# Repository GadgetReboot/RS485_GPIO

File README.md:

# RS485_GPIO
16 Switch Inputs to RS485 Control Outputs
<br><br><BR><BR>

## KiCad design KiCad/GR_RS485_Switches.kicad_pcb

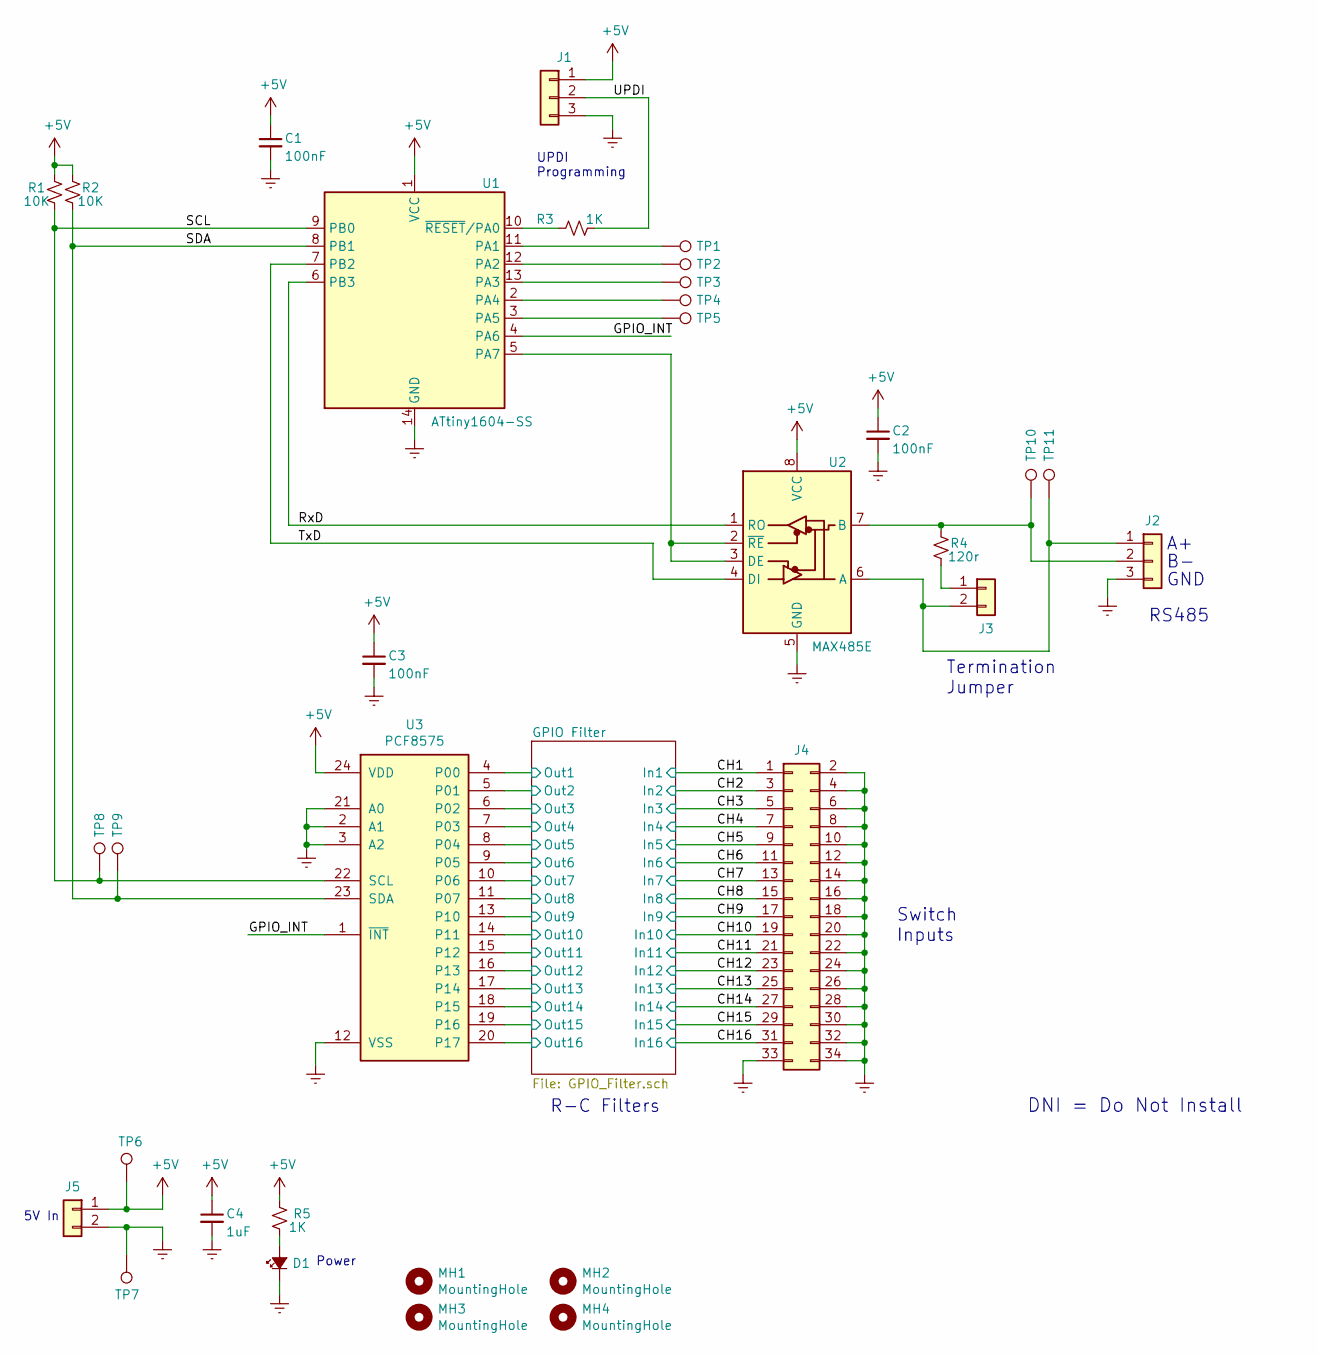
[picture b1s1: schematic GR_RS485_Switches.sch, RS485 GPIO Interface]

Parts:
C1, C2, C3: 100nF; C_0805_2012Metric_Pad1.15x1.40mm_HandSolder
C4: 1uF; C_0805_2012Metric_Pad1.15x1.40mm_HandSolder
D1: LED_Small_ALT; LED_0805_2012Metric_Pad1.15x1.40mm_HandSolder
J1: Conn_01x03; PinHeader_1x03_P2.54mm_Vertical
J2: Conn_01x03; JST_XH_S3B-XH-A-1_1x03_P2.50mm_Horizontal
J3: Conn_01x02; PinHeader_1x02_P2.54mm_Vertical
J4: Conn_02x17_Odd_Even; IDC-Header_2x17_P2.54mm_Vertical
J5: Conn_01x02; JST_XH_S2B-XH-A-1_1x02_P2.50mm_Horizontal
MH1, MH2, MH3, MH4: MountingHole; MountingHole_3.7mm
R1, R2: 10K; R_0805_2012Metric_Pad1.15x1.40mm_HandSolder
R3, R5: 1K; R_0805_2012Metric_Pad1.15x1.40mm_HandSolder
R4: 120r; R_0805_2012Metric_Pad1.15x1.40mm_HandSolder
TP1, TP2, TP3, TP4, TP5, TP6, TP7, TP8, TP9, TP10, TP11: TestPoint; TestPoint_Pad_D1.0mm
U1: ATtiny1604-SS; SOIC-14_3.9x8.7mm_P1.27mm
U2: MAX485E; SOIC-8_3.9x4.9mm_P1.27mm
U3: PCF8575; SOIC-24W_7.5x15.4mm_P1.27mm

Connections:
+5V: C1.1, C2.1, C3.1, C4.1, J1.1, J5.1, R1.2, R2.2, R5.2, TP6.1, U1.1 (VCC), U2.8 (VCC), U3.24 (VDD)
/CH1: J4.1; also elsewhere on the board
/CH2: J4.3; also elsewhere on the board
/CH3: J4.5; also elsewhere on the board
/CH4: J4.7; also elsewhere on the board
/CH5: J4.9; also elsewhere on the board
/CH6: J4.11; also elsewhere on the board
/CH7: J4.13; also elsewhere on the board
/CH8: J4.15; also elsewhere on the board
/CH9: J4.17; also elsewhere on the board
/CH10: J4.19; also elsewhere on the board
/CH11: J4.21; also elsewhere on the board
/CH12: J4.23; also elsewhere on the board
/CH13: J4.25; also elsewhere on the board
/CH14: J4.27; also elsewhere on the board
/CH15: J4.29; also elsewhere on the board
/CH16: J4.31; also elsewhere on the board
/GPIO Filter/Out1: U3.4 (P00); also elsewhere on the board
/GPIO Filter/Out2: U3.5 (P01); also elsewhere on the board
/GPIO Filter/Out3: U3.6 (P02); also elsewhere on the board
/GPIO Filter/Out4: U3.7 (P03); also elsewhere on the board
/GPIO Filter/Out5: U3.8 (P04); also elsewhere on the board
/GPIO Filter/Out6: U3.9 (P05); also elsewhere on the board
/GPIO Filter/Out7: U3.10 (P06); also elsewhere on the board
/GPIO Filter/Out8: U3.11 (P07); also elsewhere on the board
/GPIO Filter/Out9: U3.13 (P10); also elsewhere on the board
/GPIO Filter/Out10: U3.14 (P11); also elsewhere on the board
/GPIO Filter/Out11: U3.15 (P12); also elsewhere on the board
/GPIO Filter/Out12: U3.16 (P13); also elsewhere on the board
/GPIO Filter/Out13: U3.17 (P14); also elsewhere on the board
/GPIO Filter/Out14: U3.18 (P15); also elsewhere on the board
/GPIO Filter/Out15: U3.19 (P16); also elsewhere on the board
/GPIO Filter/Out16: U3.20 (P17); also elsewhere on the board
/GPIO_INT: U1.4 (PA6), U3.1 (~INT)
/RxD: U1.6 (PB3), U2.1 (RO)
/SCL: R1.1, TP8.1, U1.9 (PB0), U3.22 (SCL)
/SDA: R2.1, TP9.1, U1.8 (PB1), U3.23 (SDA)
/TxD: U1.7 (PB2), U2.4 (DI)
/UPDI: J1.2, R3.1
GNDREF: C1.2, C2.2, C3.2, C4.2, D1.1 (K), J1.3, J2.3, J4.2, J4.4, J4.6, J4.8, J4.10, J4.12, J4.14, J4.16, J4.18, J4.20, J4.22, J4.24, J4.26, J4.28, J4.30, J4.32, J4.33, J4.34, J5.2, TP7.1, U1.14 (GND), U2.5 (GND), U3.2 (A1), U3.3 (A2), U3.12 (VSS), U3.21 (A0); also elsewhere on the board
unnamed: D1.2 (A), R5.1
unnamed: J2.1, J3.2, TP11.1, U2.6 (A)
unnamed: J2.2, R4.2, TP10.1, U2.7 (B)
unnamed: J3.1, R4.1
unnamed: R3.2, U1.10 (~RESET~/PA0)
unnamed: TP1.1, U1.11 (PA1)
unnamed: TP2.1, U1.12 (PA2)
unnamed: TP3.1, U1.13 (PA3)
unnamed: TP4.1, U1.2 (PA4)
unnamed: TP5.1, U1.3 (PA5)
unnamed: U1.5 (PA7), U2.2 (~RE), U2.3 (DE)

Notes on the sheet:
5V In
UPDI Programming
DNI = Do Not Install
Switch Inputs
R-C Filters
GND
RS485
Termination Jumper
Power

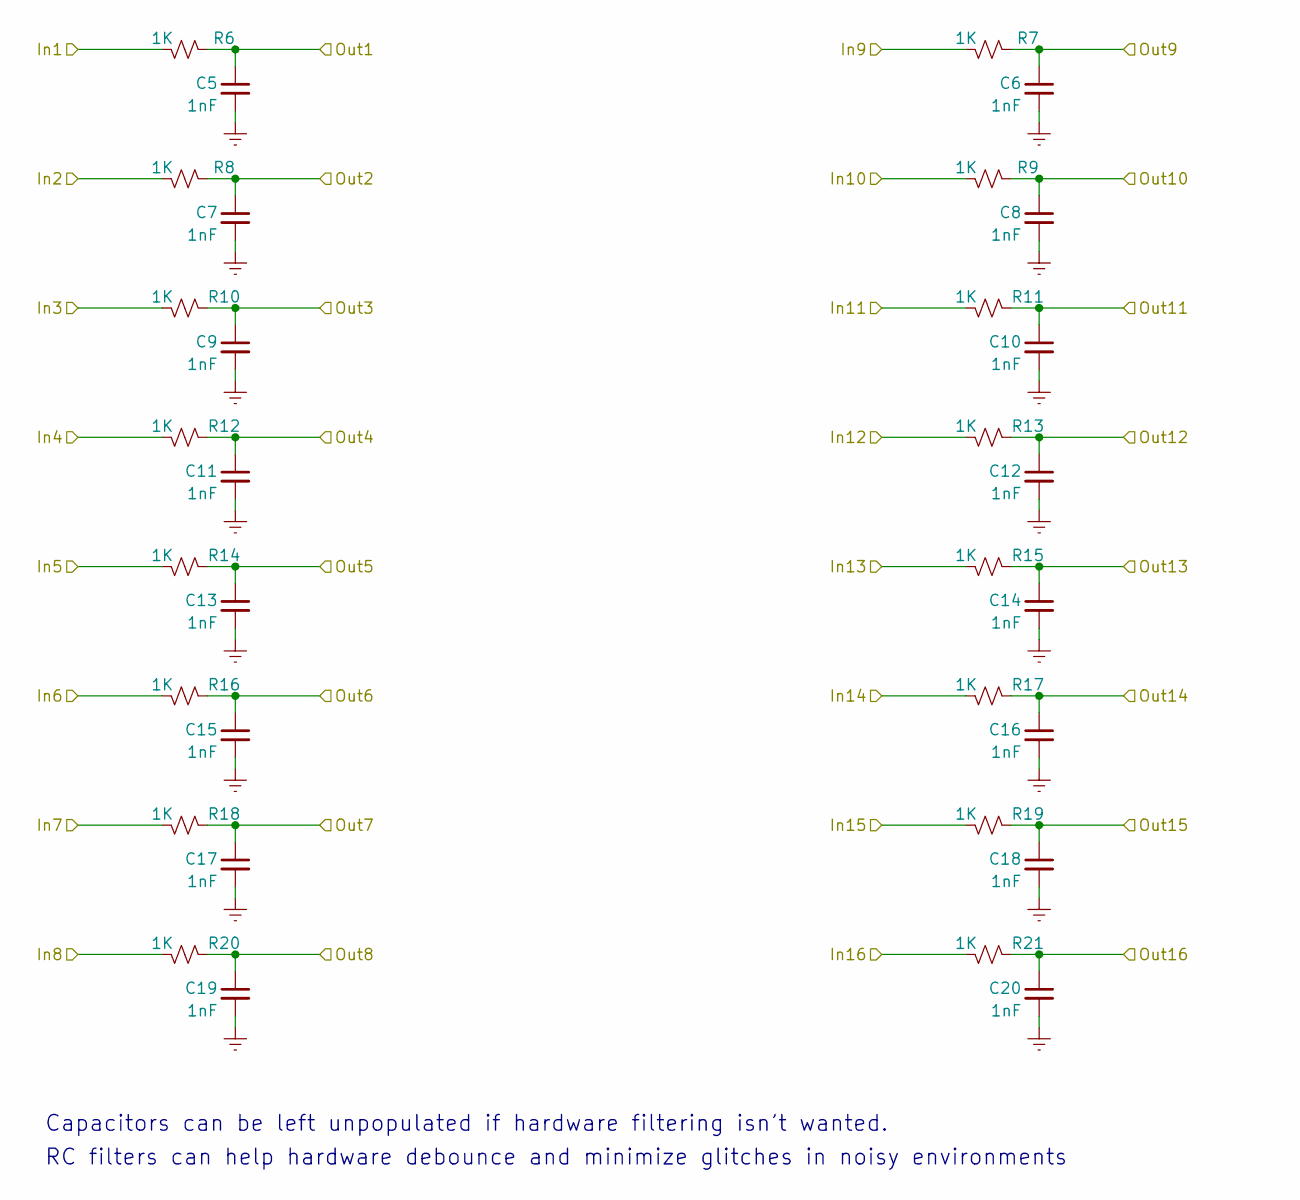
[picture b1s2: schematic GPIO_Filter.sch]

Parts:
C5, C6, C7, C8, C9, C10, C11, C12, C13, C14, C15, C16, C17, C18, C19, C20: 1nF; C_0805_2012Metric_Pad1.15x1.40mm_HandSolder
R6, R7, R8, R9, R10, R11, R12, R13, R14, R15, R16, R17, R18, R19, R20, R21: 1K; R_0805_2012Metric_Pad1.15x1.40mm_HandSolder

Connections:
/CH1: R6.1; also elsewhere on the board
/CH2: R8.1; also elsewhere on the board
/CH3: R10.1; also elsewhere on the board
/CH4: R12.1; also elsewhere on the board
/CH5: R14.1; also elsewhere on the board
/CH6: R16.1; also elsewhere on the board
/CH7: R18.1; also elsewhere on the board
/CH8: R20.1; also elsewhere on the board
/CH9: R7.1; also elsewhere on the board
/CH10: R9.1; also elsewhere on the board
/CH11: R11.1; also elsewhere on the board
/CH12: R13.1; also elsewhere on the board
/CH13: R15.1; also elsewhere on the board
/CH14: R17.1; also elsewhere on the board
/CH15: R19.1; also elsewhere on the board
/CH16: R21.1; also elsewhere on the board
/GPIO Filter/Out1: C5.1, R6.2; also elsewhere on the board
/GPIO Filter/Out2: C7.1, R8.2; also elsewhere on the board
/GPIO Filter/Out3: C9.1, R10.2; also elsewhere on the board
/GPIO Filter/Out4: C11.1, R12.2; also elsewhere on the board
/GPIO Filter/Out5: C13.1, R14.2; also elsewhere on the board
/GPIO Filter/Out6: C15.1, R16.2; also elsewhere on the board
/GPIO Filter/Out7: C17.1, R18.2; also elsewhere on the board
/GPIO Filter/Out8: C19.1, R20.2; also elsewhere on the board
/GPIO Filter/Out9: C6.1, R7.2; also elsewhere on the board
/GPIO Filter/Out10: C8.1, R9.2; also elsewhere on the board
/GPIO Filter/Out11: C10.1, R11.2; also elsewhere on the board
/GPIO Filter/Out12: C12.1, R13.2; also elsewhere on the board
/GPIO Filter/Out13: C14.1, R15.2; also elsewhere on the board
/GPIO Filter/Out14: C16.1, R17.2; also elsewhere on the board
/GPIO Filter/Out15: C18.1, R19.2; also elsewhere on the board
/GPIO Filter/Out16: C20.1, R21.2; also elsewhere on the board
GNDREF: C5.2, C6.2, C7.2, C8.2, C9.2, C10.2, C11.2, C12.2, C13.2, C14.2, C15.2, C16.2, C17.2, C18.2, C19.2, C20.2; also elsewhere on the board

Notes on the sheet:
Capacitors can be left unpopulated if hardware filtering isn’t wanted.
RC filters can help hardware debounce and minimize glitches in noisy environments

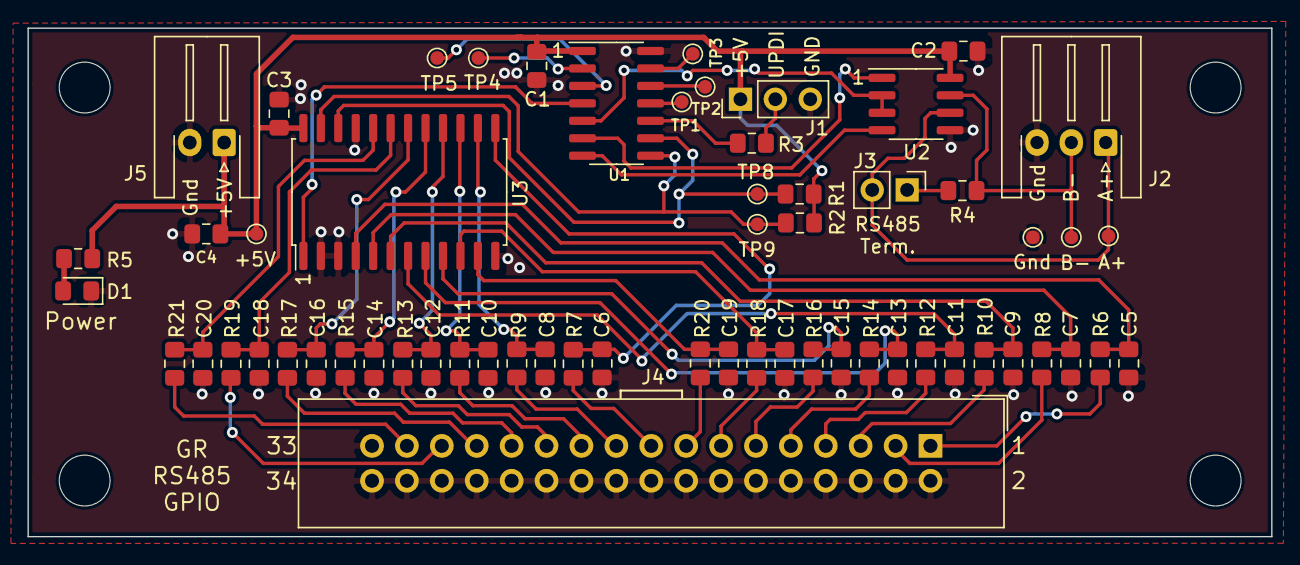
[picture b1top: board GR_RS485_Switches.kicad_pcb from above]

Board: 2 copper layers, 90.5 x 37.0 mm, 65 parts (0 on the bottom side), 51 nets.
